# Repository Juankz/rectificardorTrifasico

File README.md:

# Rectificardor Trifasico
Código de microcontrolador + Esquemas de Hardware para un rectificador trifásico totalmente controlado

Se utilizaron los siguientes programas de software: PlatformIO para programar el microcontrolador. Eagle para diseño de PCB

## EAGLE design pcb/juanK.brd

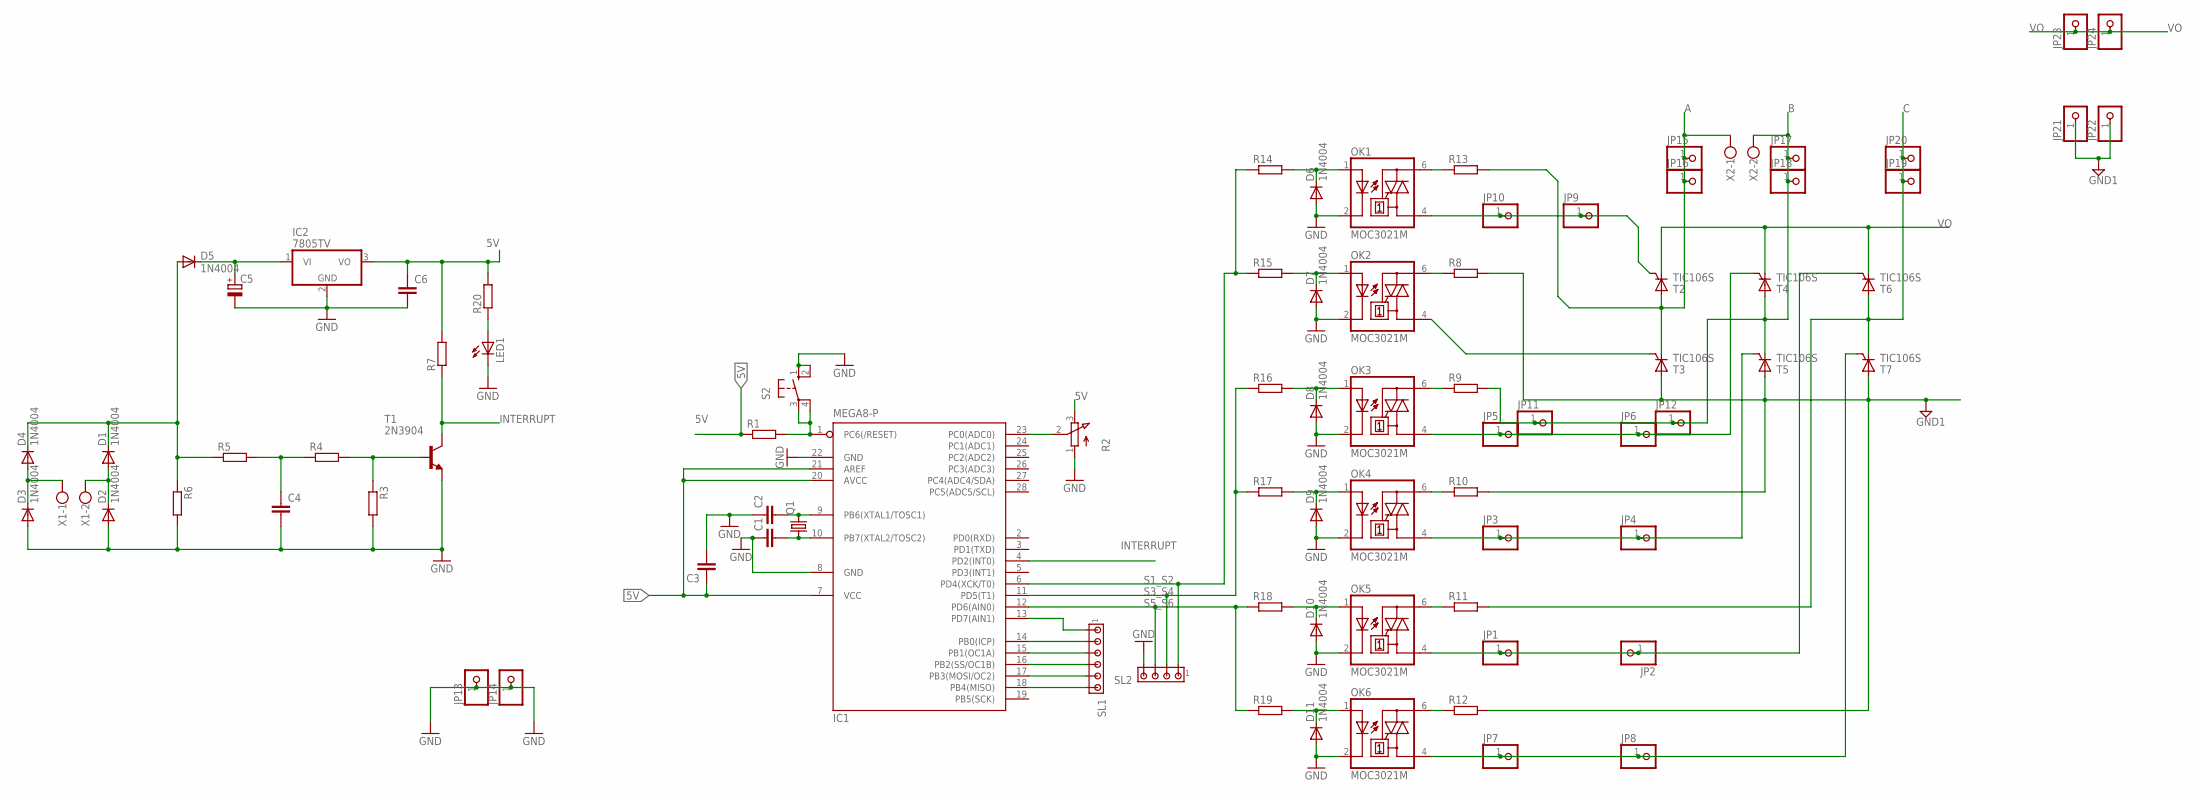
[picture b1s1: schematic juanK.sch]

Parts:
C1, C2, C3: C2,5-3; C2.5-3
C4, C6: C-EU025-025X050; C025-025X050
C5: CPOL-EUE5-10.5; E5-10,5
D1, D2, D3, D4, D5, D6, D7, D8, D9, D10, D11: 1N4004; DO41-10
IC1: MEGA8-P; DIL28-3
IC2: 7805TV; TO220V
JP1, JP2, JP3, JP4, JP5, JP6, JP7, JP8, JP9, JP10, JP11, JP12, JP13, JP14, JP15, JP16, JP17, JP18, JP19, JP20, JP21, JP22, JP23, JP24: PINHD-1X1; 1X01
LED1: LED3MM
OK1, OK2, OK3, OK4, OK5, OK6: MOC3021M; DIL06
Q1: CRYSTALHC49U70; HC49U70
R1, R20: R-EU_0204/5; 0204/5
R2: 3RP/1610N
R3, R4, R5, R6, R7: R0204/7; 0204/7
R8, R9, R10, R11, R12, R13: R-EU_0817/22; P0817/22
R14, R15, R16, R17, R18, R19: R-EU_0204/7; 0204/7
S2: 10-XX; B3F-10XX
SL1: MTA06-100; 10X06MTA
SL2: MTA04-100; 10X04MTA
T1: 2N3904; TO92
T2, T3, T4, T5, T6, T7: TIC106S
X1, X2: W237-102

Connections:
5V: C3.1, C6.1, IC1.7 (VCC), IC1.20 (AVCC), IC1.21 (AREF), IC2.3 (VO), R1.1, R2.3 (E), R7.2, R20.2
A: JP15.1, JP16.1, R13.2, T2.A, T3.C, X2.1
B: JP11.1, JP12.1, JP17.1, JP18.1, R9.2, T4.A, T5.C, X2.2
C: JP19.1, JP20.1, R11.2, T6.A, T7.C
GND: C1.1, C2.1, C3.2, C4.2, C5.-, C6.2, D2.A, D3.A, D6.A, D7.A, D8.A, D9.A, D10.A, D11.A, IC1.8 (GND), IC1.22 (GND), IC2.2 (GND), JP13.1, JP14.1, LED1.K (C), OK1.2 (C), OK2.2 (C), OK3.2 (C), OK4.2 (C), OK5.2 (C), OK6.2 (C), R2.1 (A), R3.2, R6.2, S2.1 (S), S2.2 (S1), SL2.4, T1.3 (E)
GND1: JP21.1, JP22.1, R8.2, R10.2, R12.2, T3.A, T5.A, T7.A
INTERRUPT: IC1.4 (PD2(INT0)), R7.1, T1.1 (C)
unnamed: C4.1, R4.1, R5.2
unnamed: R3.1, R4.2, T1.2 (B)
unnamed: C5.+, D5.C, IC2.1 (VI)
unnamed: OK2.6 (A2), R8.1
unnamed: D1.C, D4.C, D5.A, R5.1, R6.1
unnamed: JP9.1, JP10.1, OK1.4 (A1), T2.G
unnamed: IC1.23 (PC0(ADC0)), R2.2 (S)
unnamed: JP1.1, JP2.1, OK5.4 (A1), T6.G
unnamed: IC1.14 (PB0(ICP)), SL1.2
unnamed: D3.C, D4.A, X1.1
unnamed: D1.A, D2.C, X1.2
unnamed: IC1.15 (PB1(OC1A)), SL1.3
unnamed: LED1.A, R20.1
unnamed: C2.2, IC1.9 (PB6(XTAL1/TOSC1)), Q1.2
unnamed: C1.2, IC1.10 (PB7(XTAL2/TOSC2)), Q1.1
unnamed: IC1.1 (PC6(/RESET)), R1.2, S2.3, S2.4 (P1)
unnamed: OK1.6 (A2), R13.1
unnamed: OK3.6 (A2), R9.1
unnamed: IC1.16 (PB2(SS/OC1B)), SL1.4
unnamed: OK2.4 (A1), T3.G
unnamed: IC1.17 (PB3(MOSI/OC2)), SL1.5
unnamed: JP5.1, JP6.1, OK3.4 (A1), T4.G
unnamed: OK4.6 (A2), R10.1
unnamed: JP7.1, JP8.1, OK6.4 (A1), T7.G
unnamed: JP3.1, JP4.1, OK4.4 (A1), T5.G
unnamed: OK5.6 (A2), R11.1
unnamed: OK6.6 (A2), R12.1
unnamed: D6.C, OK1.1 (A), R14.2
unnamed: D7.C, OK2.1 (A), R15.2
unnamed: D8.C, OK3.1 (A), R16.2
unnamed: D9.C, OK4.1 (A), R17.2
unnamed: D10.C, OK5.1 (A), R18.2
unnamed: D11.C, OK6.1 (A), R19.2
unnamed: IC1.18 (PB4(MISO)), SL1.6
unnamed: IC1.13 (PD7(AIN1)), SL1.1
S1_S2: IC1.6 (PD4(XCK/T0)), R14.1, R15.1, SL2.1
S3_S4: IC1.11 (PD5(T1)), R16.1, R17.1, SL2.2
S5_S6: IC1.12 (PD6(AIN0)), R18.1, R19.1, SL2.3
VO: JP23.1, JP24.1, T2.C, T4.C, T6.C

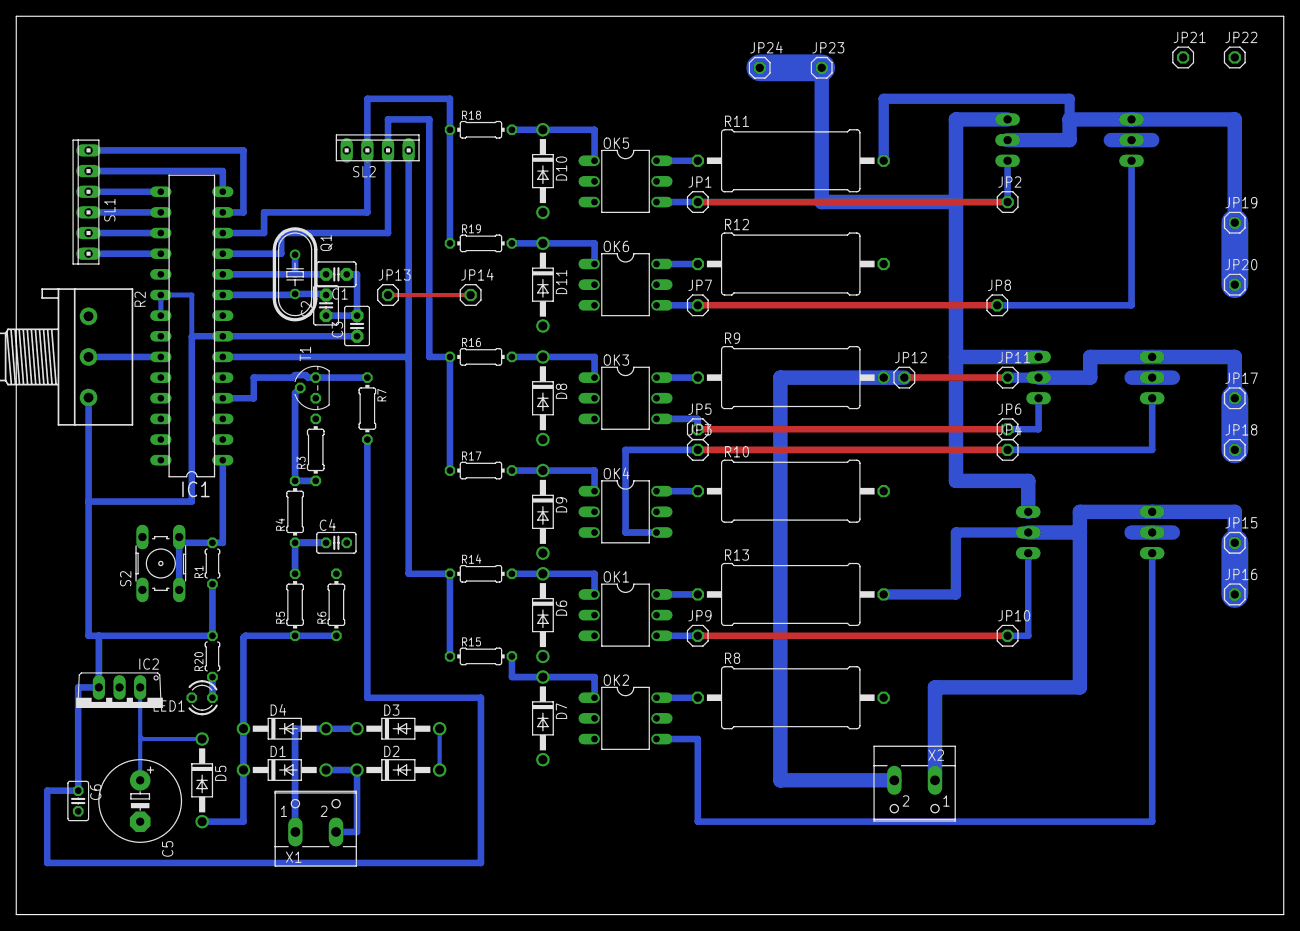
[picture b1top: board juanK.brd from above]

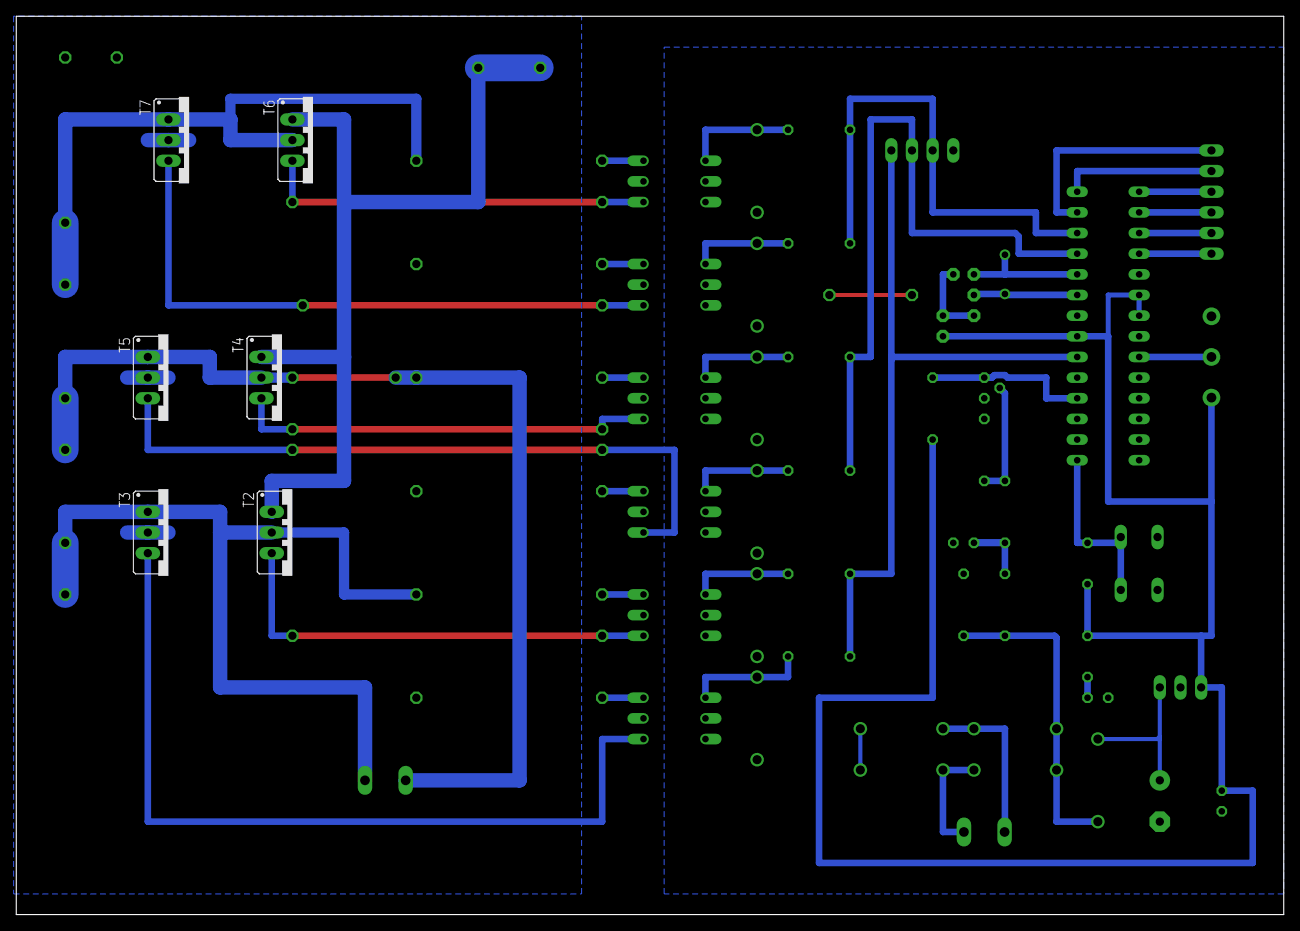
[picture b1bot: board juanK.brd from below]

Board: 2 copper layers, 155.9 x 110.5 mm, 83 parts (6 on the bottom side), 46 nets.

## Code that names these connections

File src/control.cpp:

#include <Arduino.h>

#define DEBUG 0

const int S1_S2 = 4;
const int S3_S4 = 5;
const int S5_S6 = 6;

const int pinLed = 13;
const int pinCrucex0 = 2;
const int pinAlfa = A0; //Entrada del potenciómetro que medirá el ángulo alfa
const int f = 60;
const float DaG = float(180)/float(1023); //Digital a Grados
const float DaMicros = float(1)/float(1023); //Digital a microsegundos
const float DIF_PULSOS_GRADOS=60;
const float CAMBIO_FASE_GRADOS=35; //30 + 5 grados de tolerancia

/* Estados */
const short ESPERAR_ALFA = 0;
const short DISPARANDO = 1;
const short ESPERANDO_SIG_PULSO = 2;
const short APAGAR = 3;
short estado = ESPERAR_ALFA;

/* Timers microsegundos*/
long ultimo_t0;
long ultimo_t1;
long actual_t0;
long actual_t1;
long ultimo_t2_cruce;
long ultimo_t3_cruce;

/* Trifasica */
int senales[6]; // Secuencia: ACN - CNB - ANB - ANC - CBN - ABN
int pines_senales[] = {7,8,9,10,11,12};
int senal_actual = 6;

boolean cruce_detectado = false;
short contador_cruces = 0;
float T = (1/(2*(float)f))*1000000; //Un solo semiciclo. us
int valorAlfaSensado; //Alamcena el valor del divisor de voltaje por potenciómetro
int alfa = 10; //Valor entre 0 y 180
float alfaMicroseconds; //valor en us
float anchoPulso = 0.07*T; // Valor en us
float dif_pulsos_us=(DIF_PULSOS_GRADOS/float(360*60))*1000000;
float cambio_fase_us = (CAMBIO_FASE_GRADOS/float(f*360))*1000000;

int obtener_prox_senal(int s){
  if(s >= 5){
    return 0;
  }else{
    return s+1;
  }
}

void cruce(){
  actual_t1 = micros();
  /*Aseguramos que solo tome el cruce de un semiciclo*/
  if(actual_t1-ultimo_t1>T*1.5){
    ultimo_t1 = micros();
    cruce_detectado = true;
    // ultimo_t0=micros();
  }
}

void setup(){
  #if DEBUG
    Serial.begin(9600);
  #endif
  pinMode(pinCrucex0, INPUT_PULLUP);
  pinMode(S1_S2,OUTPUT);
  pinMode(S3_S4,OUTPUT);
  pinMode(S5_S6,OUTPUT);
  for(int i = 0; i < 6; i++){
    pinMode(pines_senales[i],OUTPUT);
  }
  attachInterrupt(digitalPinToInterrupt(pinCrucex0), cruce, FALLING);
  ultimo_t1 = micros();
}

void loop(){
  noInterrupts();
  valorAlfaSensado = analogRead(pinAlfa);
  interrupts();


  alfa = valorAlfaSensado*DaG;

  if(alfa > 111){
    alfa = 111;
  }
  alfaMicroseconds = T*alfa/180;

  /* Calcular*/
  noInterrupts();
  boolean cruce_detectado_copia = cruce_detectado;
  interrupts();

  float alfa_real_us = cambio_fase_us+alfaMicroseconds;

  if(cruce_detectado_copia){
    actual_t0 = micros();
    int prox_senal = obtener_prox_senal(senal_actual);

    switch (estado) {

      /*Una vez que llegue al alfa, escribir las dos señales en alto*/
      case ESPERAR_ALFA:
        if(actual_t0 - ultimo_t1 > alfa_real_us){
          senales [senal_actual] = HIGH;
          senales [prox_senal] = HIGH;
          digitalWrite(pines_senales[senal_actual],HIGH);
          digitalWrite(pines_senales[prox_senal],HIGH);
          ultimo_t0 = micros();
          estado=DISPARANDO;
        }
        break;

      /* Cuando el tiempo ha sobrepasado el ancho del pulso, apaga las señales y continúa con la
         siguiente señal. Si ya ha disparado todas las señales, salga y espera al siguiente cruce por cero
      */
      case DISPARANDO:
        if(actual_t0 - ultimo_t0 > anchoPulso){
          senales [senal_actual] = LOW;
          senales [prox_senal] = LOW;
          digitalWrite(pines_senales[senal_actual],LOW);
          digitalWrite(pines_senales[prox_senal],LOW);
          senal_actual=prox_senal;
          if(senal_actual<5){
            estado = ESPERANDO_SIG_PULSO;
          }else{
            estado = APAGAR;
          }
        }
        break;

      case ESPERANDO_SIG_PULSO:
        if(actual_t0 - ultimo_t0 > dif_pulsos_us){
          senales [senal_actual] = HIGH;
          senales [prox_senal] = HIGH;
          digitalWrite (pines_senales[senal_actual],HIGH);
          digitalWrite (pines_senales[prox_senal],HIGH);
          ultimo_t0 = micros ();
          estado = DISPARANDO;
        }
        break;

      case APAGAR:
        /* Salir */
        if(actual_t0-ultimo_t1<T*1.5){
          estado = ESPERAR_ALFA;
        }else{
          cruce_detectado=false;
        }
        break;

      default:
        // cruce_detectado=false;
        break;
    }
  }

  int valor_S1_S2 = senales[0] | senales[3];
  int valor_S3_S4 = senales[2] | senales[5];
  int valor_S5_S6 = senales[1] | senales[4];

  digitalWrite(S1_S2, valor_S1_S2);
  digitalWrite(S3_S4, valor_S3_S4);
  digitalWrite(S5_S6, valor_S5_S6);


  //====================================================
  #if DEBUG
    Serial.println("=================================");
    // Serial.print("f(Hz): ");
    // Serial.println(f);
    // Serial.print("T(us): ");
    // Serial.println(T);
    // Serial.print("DaG: ");
    // Serial.println(DaG);
    // Serial.print("valor de alfa sensado: ");
    // Serial.println(valorAlfaSensado);
    Serial.print("alfa(°): ");
    Serial.println(alfa);
    Serial.print("alfa(us)): ");
    Serial.println(alfaMicroseconds);
    // Serial.print("anchoPulso(us): ");
    // Serial.println(anchoPulso);
  #endif
}

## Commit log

2017-06-21 Añadir control fase preliminar
2017-06-21 Añadir opción de debug por puerto serial
2017-06-27 Corregir delay en microsegundos
2017-06-29 Cambiar a multitarea
2017-06-29 Añadir señales de control con salida digital
2017-06-29 Agregar salidas a los SCR y de observación
2017-06-29 Ajustar presición
2017-06-30 Añadir esquemáticos y PCB
2017-06-30 Ordenar elementos y Optimizar caminos
2017-06-30 Diseño de PCB terminado
2017-07-08 Corregir dimensiones de algunos componentes
2017-07-10 Incrementar espacio entre pista y tierra e incrementar ancho de las pistas
2017-08-01 Corregir conexión de tierra en los MOC
